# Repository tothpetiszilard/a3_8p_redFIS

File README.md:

# Audi A3 8P Red FIS Project
<b>This is a project about discovering (reverse-engineering) Audi A3 8P dashboard's Driver Information System and its protocol.</b>

For people who don't know what is DIS or FIS:
https://www.youtube.com/watch?v=bKFak5AGAGo

The goal is to implement a similiar but simpler open-source alternative to the "FIS-Control" or "Polar FIS".<br>
https://fis-control.de/index_en.html<br>
https://www.urotuning.com/products/polar-fis-advanced-multi-function-display-pf-04?variant=8384889323575

<b> Picture about the current status:</b><br>

## Connections description
https://github.com/tothpetiszilard/a3_8p_redFIS/blob/main/connection.md

## Compatibility:
Selectable in "menuconfig":
- You can use Alternative VWTP CANID if you have RNS-E (Audi navigation with color display) installed and your dashboards part number is "8P0 920 930". Don't select "FIS-Control" in your RNS-E custom firmware in this case. Enter/exit FIS scenarios are a bit buggy.

- You have to use Navigation VWTP CANID if you have dashboard with part number "8P0 920 931". Alternative CANID is not supported by the dash. 

You may select "FIS-Control" in your RNS-E custom firmware in this case, and RedFIS will do the routing of the display data from RNS-E to the Dash - if that last "page" is selected using the Up/Down stalk buttons. This feature can be enabled (or disabled) in the menuconfig.
Default state is enabled, since my car has a navigation with custom firmware and "FIS-Control" option enabled.

<i>Brave volunteers are warmly welcomed for testing... :)</i>

Used and helpful sources:<br>
https://docs.google.com/spreadsheets/d/1eirT8LbSRl4j06BpwgsiE4PM_2BGH9UStdWLXwKvHJw/edit#gid=10<br>
https://i-wiki.tech/?post=vw-transport-protocol-20-tp-20-for-can-bus<br>
http://www.orlaus.dk/mercantec/UdvidetHardwareSoftware/Can/OBD2/VW%20Transport%20Protocol%202.0%20(TP%202.0)%20for%20CAN%20bus%20_%20jazdw.pdf<br>
https://github.com/openvehicles/Open-Vehicle-Monitoring-System-3/blob/master/vehicle/OVMS.V3/components/vehicle/docs/VW-TP-2.0.txt<br>

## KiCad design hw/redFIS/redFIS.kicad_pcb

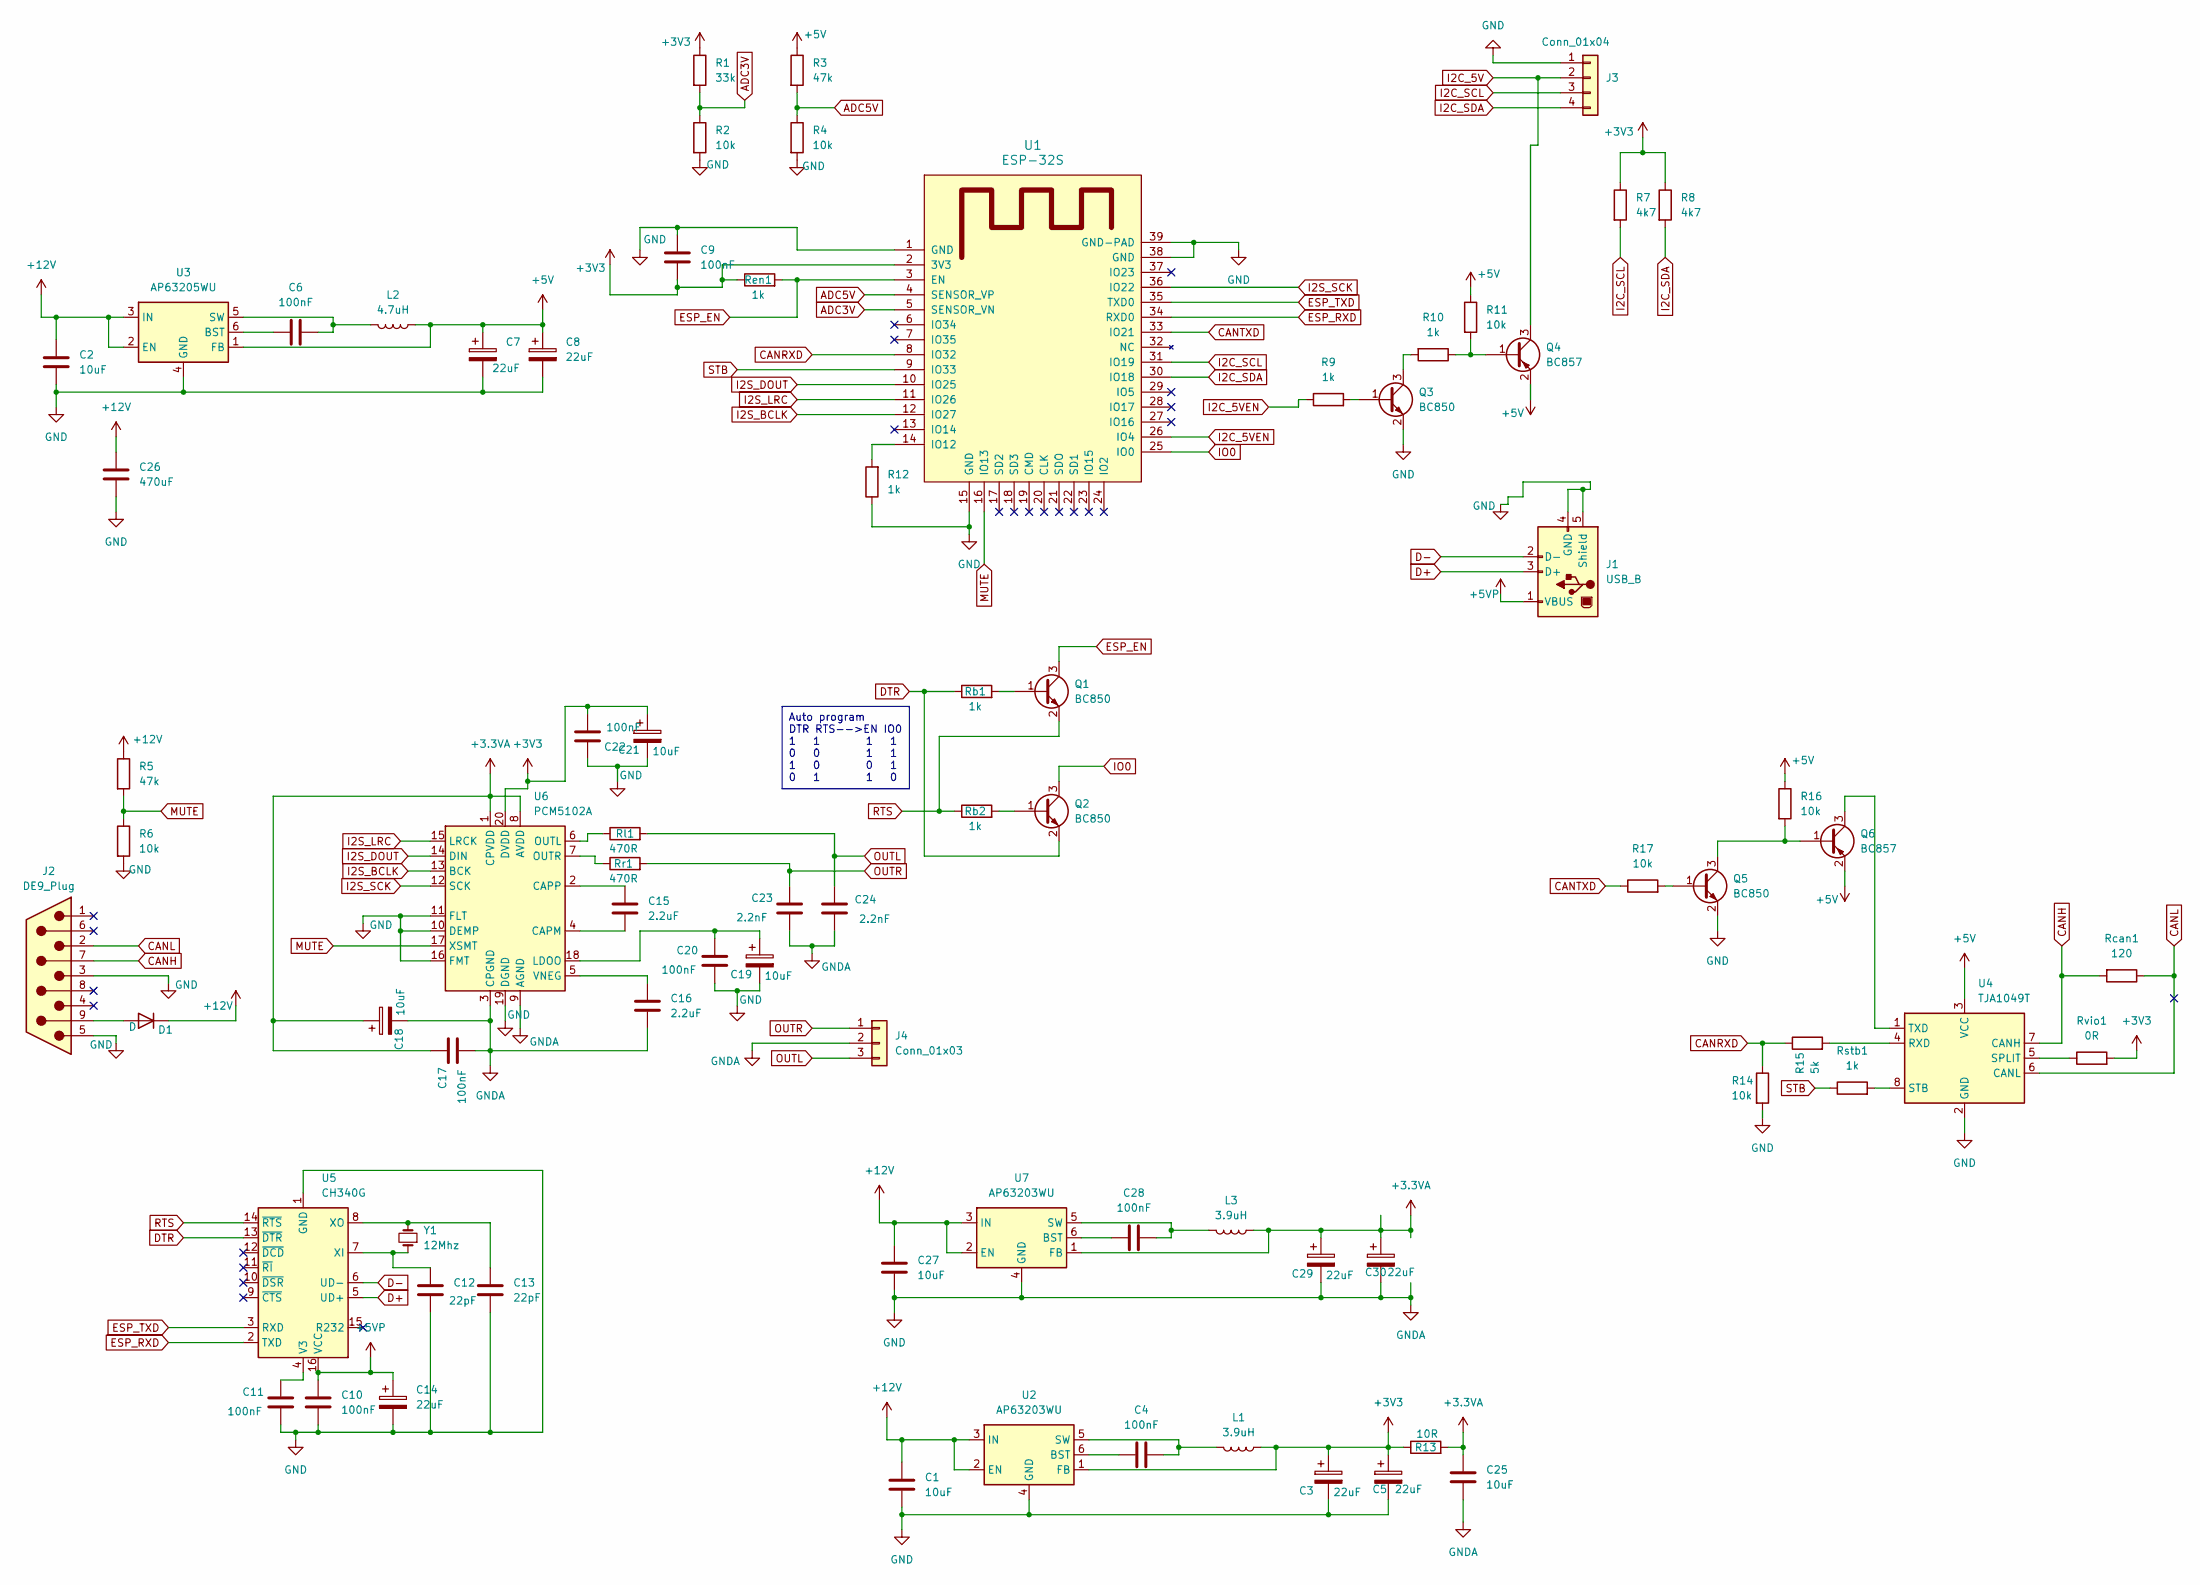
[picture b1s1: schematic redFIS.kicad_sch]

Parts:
C1, C2, C18, C19, C21, C25, C27: 10uF; C_0603_1608Metric_Pad1.08x0.95mm_HandSolder
C3, C5, C7, C8, C14, C29, C30: 22uF; C_1210_3225Metric_Pad1.33x2.70mm_HandSolder
C4, C6, C9, C10, C11, C17, C20, C22, C28: 100nF; C_0603_1608Metric_Pad1.08x0.95mm_HandSolder
C12, C13: 22pF; C_0603_1608Metric_Pad1.08x0.95mm_HandSolder
C15, C16: 2.2uF; C_0603_1608Metric_Pad1.08x0.95mm_HandSolder
C23, C24: 2.2nF; C_0603_1608Metric_Pad1.08x0.95mm_HandSolder
C26: 470uF; CP_Radial_D16.0mm_P7.50mm
D1: D; D_SMB_Handsoldering
J1: USB_B; USB_B_OST_USB-B1HSxx_Horizontal
J2: DE9_Plug; DSUB-9_Male_EdgeMount_P2.77mm
J3: Conn_01x04; PinHeader_1x04_P2.54mm_Vertical
J4: Conn_01x03; PinHeader_1x03_P2.54mm_Vertical
L1, L3: 3.9uH; L_TracoPower_TCK-047_5.2x5.8mm
L2: 4.7uH; L_TracoPower_TCK-047_5.2x5.8mm
Q1, Q2: BC850; SOT-23_Handsoldering
Q3, Q5: BC850; SOT-23
Q4, Q6: BC857; SOT-23
R1: 33k; R_0603_1608Metric_Pad0.98x0.95mm_HandSolder
R2, R4, R6, R11, R14, R16, R17: 10k; R_0603_1608Metric_Pad0.98x0.95mm_HandSolder
R3, R5: 47k; R_0603_1608Metric_Pad0.98x0.95mm_HandSolder
R7, R8: 4k7; R_0603_1608Metric_Pad0.98x0.95mm_HandSolder
R9, R10, R12: 1k; R_0603_1608Metric_Pad0.98x0.95mm_HandSolder
R13: 10R; R_1206_3216Metric_Pad1.30x1.75mm_HandSolder
R15: 5k; R_0603_1608Metric_Pad0.98x0.95mm_HandSolder
Rb1, Rb2: 1k; R_0603_1608Metric_Pad0.98x0.95mm_HandSolder
Rcan1: 120; R_0603_1608Metric_Pad0.98x0.95mm_HandSolder
Ren1: 1k; R_0603_1608Metric_Pad0.98x0.95mm_HandSolder
Rl1: 470R; R_0603_1608Metric_Pad0.98x0.95mm_HandSolder
Rr1: 470R; R_0603_1608Metric_Pad0.98x0.95mm_HandSolder
Rstb1: 1k; R_0603_1608Metric_Pad0.98x0.95mm_HandSolder
Rvio1: 0R; R_0603_1608Metric_Pad0.98x0.95mm_HandSolder
U1: ESP-32S
U2, U7: AP63203WU; TSOT-23-6
U3: AP63205WU; TSOT-23-6
U4: TJA1049T; SOIC-8_3.9x4.9mm_P1.27mm
U5: CH340G; SOIC-16_3.9x9.9mm_P1.27mm
U6: PCM5102A; TSSOP-20_4.4x6.5mm_P0.65mm
Y1: 12Mhz; Crystal_SMD_HC49-SD_HandSoldering

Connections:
+3.3VA: C17.2, C18.1, C25.1, C29.1, C30.1, L3.1, R13.2, U6.1 (CPVDD), U6.8 (AVDD), U7.1 (FB)
+3V3: C3.1, C5.1, C9.1, C21.1, C22.1, L1.1, R1.1, R7.1, R8.1, R13.1, Ren1.1, Rvio1.2, U1.2 (3V3), U2.1 (FB), U6.20 (DVDD)
+5V: C7.1, C8.1, L2.1, Q4.2 (E), Q6.2 (E), R3.1, R11.1, R16.1, U3.1 (FB), U4.3 (VCC)
+5VP: C10.2, C14.1, J1.1 (VBUS), U5.16 (VCC)
+12V: C1.1, C2.1, C26.1, C27.1, D1.1 (K), R5.1, U2.2 (EN), U2.3 (IN), U3.2 (EN), U3.3 (IN), U7.2 (EN), U7.3 (IN)
ADC3V: R1.2, R2.1, U1.5 (SENSOR_VN)
ADC5V: R3.2, R4.1, U1.4 (SENSOR_VP)
CANH: J2.7, Rcan1.2, U4.7 (CANH)
CANL: J2.2, Rcan1.1, U4.6 (CANL)
CANRXD: R14.1, R15.1, U1.8 (IO32)
CANTXD: R17.1, U1.33 (IO21)
D+: J1.3 (D+), U5.5 (UD+)
D-: J1.2 (D-), U5.6 (UD-)
DTR: Q2.2 (E), Rb1.1, U5.13 (~DTR)
ESP_EN: Q1.3 (C), Ren1.2, U1.3 (EN)
ESP_RXD: U1.34 (RXD0), U5.2 (TXD)
ESP_TXD: U1.35 (TXD0), U5.3 (RXD)
GND: C1.2, C2.2, C3.2, C5.2, C7.2, C8.2, C9.2, C10.1, C11.1, C12.1, C13.1, C14.2, C16.2, C17.1, C18.2, C19.2, C20.1, C21.2, C22.2, C23.1, C24.1, C25.2, C26.2, C27.2, C29.2, C30.2, J1.4 (GND), J1.5 (Shield), J2.3, J2.5, J3.1, J4.2, Q3.2 (E), Q5.2 (E), R2.2, R4.2, R6.2, R12.1, R14.2, U1.1 (GND), U1.15 (GND), U1.38 (GND), U1.39 (GND-PAD), U2.4 (GND), U3.4 (GND), U4.2 (GND), U5.1 (GND), U6.3 (CPGND), U6.9 (AGND), U6.10 (DEMP), U6.11 (FLT), U6.16 (FMT), U6.19 (DGND), U7.4 (GND)
I2C_5V: J3.2, Q4.3 (C)
I2C_5VEN: R9.1, U1.26 (IO4)
I2C_SCL: J3.3, R7.2, U1.31 (IO19)
I2C_SDA: J3.4, R8.2, U1.30 (IO18)
I2S_BCLK: U1.12 (IO27), U6.13 (BCK)
I2S_DOUT: U1.10 (IO25), U6.14 (DIN)
I2S_LRC: U1.11 (IO26), U6.15 (LRCK)
I2S_SCK: U1.36 (IO22), U6.12 (SCK)
IO0: Q2.3 (C), U1.25 (IO0)
MUTE: R5.2, R6.1, U1.16 (IO13), U6.17 (XSMT)
unnamed: D1.2 (A), J2.9
unnamed: Q1.1 (B), Rb1.2
unnamed: Q2.1 (B), Rb2.2
unnamed: Q3.1 (B), R9.2
unnamed: Q3.3 (C), R10.2
unnamed: Q4.1 (B), R10.1, R11.2
unnamed: Q5.1 (B), R17.2
unnamed: Q5.3 (C), Q6.1 (B), R16.2
unnamed: Q6.3 (C), U4.1 (TXD)
unnamed: R12.2, U1.14 (IO12)
unnamed: C4.1, U2.6 (BST)
unnamed: C4.2, L1.2, U2.5 (SW)
unnamed: C6.1, U3.6 (BST)
unnamed: C6.2, L2.2, U3.5 (SW)
unnamed: R15.2, U4.4 (RXD)
unnamed: Rvio1.1, U4.5 (SPLIT)
unnamed: Rstb1.2, U4.8 (STB)
unnamed: C11.2, U5.4 (V3)
unnamed: C12.2, U5.7 (XI), Y1.1
unnamed: C13.2, U5.8 (XO), Y1.2
unnamed: C15.2, U6.4 (CAPM)
unnamed: C15.1, U6.2 (CAPP)
unnamed: C19.1, C20.2, U6.18 (LDOO)
unnamed: Rl1.1, U6.6 (OUTL)
unnamed: Rr1.1, U6.7 (OUTR)
unnamed: C16.1, U6.5 (VNEG)
unnamed: C28.1, U7.6 (BST)
unnamed: C28.2, L3.2, U7.5 (SW)
OUTL: C24.2, J4.3, Rl1.2
OUTR: C23.2, J4.1, Rr1.2
RTS: Q1.2 (E), Rb2.1, U5.14 (~RTS)
STB: Rstb1.1, U1.9 (IO33)

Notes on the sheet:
Auto program DTR RTS-->EN IO0 1 1 1 1 0 0 1 1 1 0 0 1 0 1 1 0

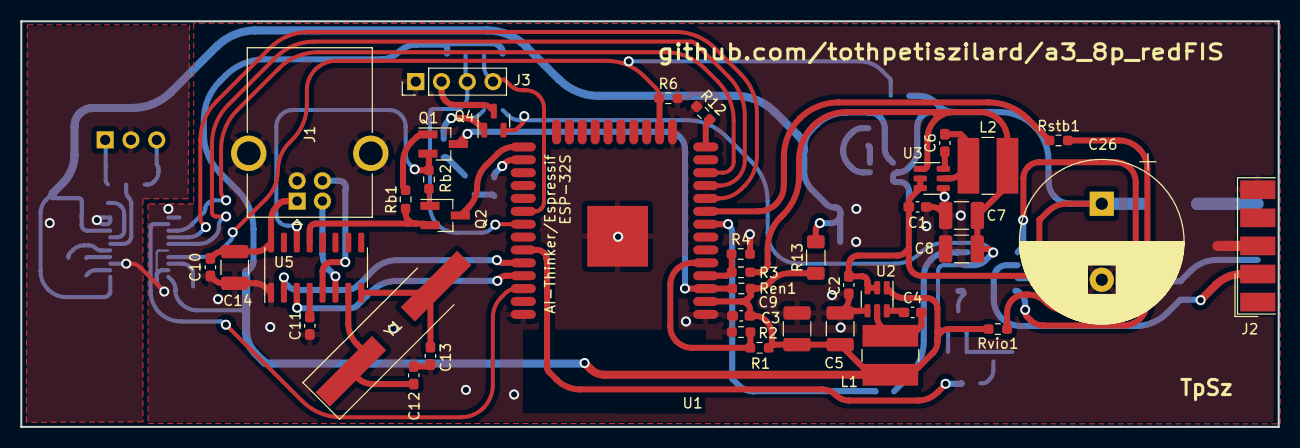
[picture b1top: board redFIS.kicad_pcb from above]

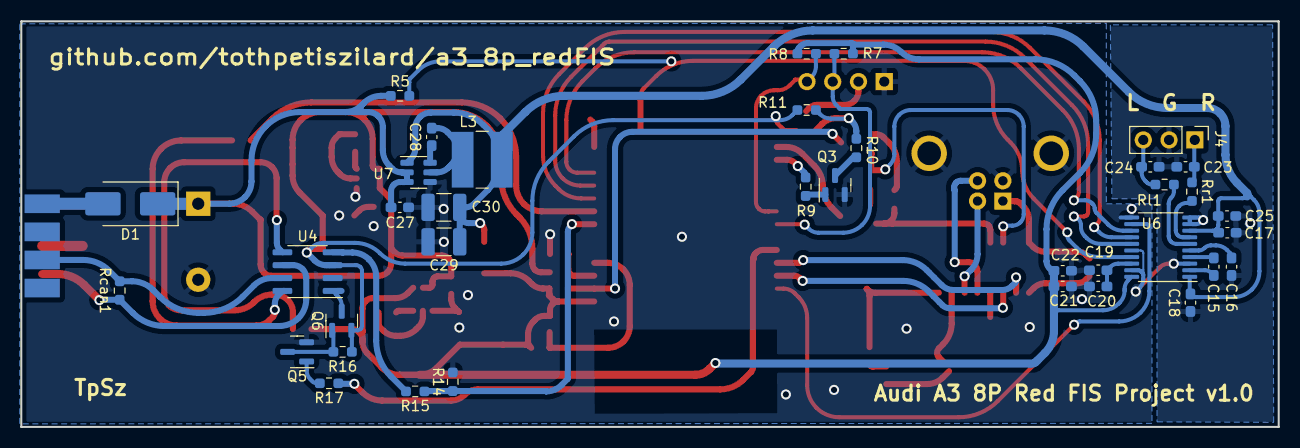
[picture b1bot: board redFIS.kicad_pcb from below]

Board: 2 copper layers, 124.0 x 40.0 mm, 77 parts (37 on the bottom side), 60 nets.

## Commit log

2022-11-19 Update README.md
    Update project description
2022-11-19 Added some collected information as text documents
2022-11-19 No duplicates
2022-11-23 Started coding: VwTP + CAN wrapper added -> test results: TP channel can be opened
2022-11-24 First running 'demo' version on ESP32 hw, no real functionality yet, just a feasibility study
2022-11-24 Added evidence on that it works
2022-11-24 Added picture
2022-11-24 Bugfixes: VWTP: Resend + wait for ack; DashApp: switched to small font as the comment says
2022-11-24 Configured CAN acceptance filter
2022-11-24 Added support for stalk buttons
2022-11-24 Started implementation of kwp2000 diagnostics support
2022-11-25 VWTP improvements and bugfix for diagnostics
2022-11-28 Feature update for DashApp, improved robustness for the project
2022-11-28 VWTP feature upgrade
2022-11-28 Bugfixes + ASCII fix added
2022-12-05 Not the cleanest code ever, but does something
2022-12-05 Replaced image in description
2022-12-08 Improved stability, removed debug code
2022-12-09 Little bugfixes and VWTP upgrade
2022-12-09 VWTP improvements
2022-12-09 KWP2000: Handling timeouts, try reconnect if needed, handling corrupt TP packets
2022-12-14 Single-thread version of the software for testing purposes
2022-12-22 Bugfix: KWP2000 timeout handling was incorrect
2022-12-22 Increased CAN RX buffer size
2022-12-22 Fixed a bug in Kwp2000 timeout handling
2022-12-22 Bad bugfix..
2022-12-23 Update canWrapper.c
    Fixing a huge but well hidden bug. CAN of course shall resend the frame if it lost the arbitration ...
2022-12-23 Fixed a well hidden bug in CAN config
2022-12-24 Added page switching to DIS
2022-12-24 Fix build
2022-12-24 Update DIS
2022-12-24 Remove debug code, slight improvements
2023-03-22 Added ignition detection to DashApp and KWP, adapted can filter, did some changes on DIS
2023-03-23 Primitive ignition handling and sleep mode with wakeup on CAN msg
2023-03-24 Added new menuconfig, now navigation or auto transmission channel can be selected. Adapted code accordingly. Added enter/exit feature (necessary while using auto trans ch)
2023-03-25 Fixed namings - wrong assumption
2023-03-25 Updated README for version 0.2
2023-03-25 Cosmetics in README
2023-03-25 Excluding KL_S from ignition status
2023-03-26 Cosmetics - Added comments
2023-03-26 Redesigned diagnostics - added dashboard diag module
2023-03-26 Updated KWP2000 module
2023-03-26 Added 'Bench test mode'
2023-12-21 Started unit-tests for VWTP component
2023-12-21 Undate code to v0_2, unstable version
2023-12-21 VWTP fixes and more unit-tests
2023-12-21 Add more test-cases for VWTP
2023-12-21 Added unit-test for stalk_buttons
2023-12-22 Added unit-test for DashApp
2023-12-22 Improved bench test mode in DIS
2023-12-25 Small fixes in the 'old' code
2023-12-25 Up and Down stalkbuttons were mixed up
2023-12-25 Beta version of VWTP routing between Nav and Dash
2024-06-23 New routing concept - NOT TESTED YET
2024-07-04 New routing concept - Bugfix
2024-07-04 Bugfix for switching between diag and nav routing screens
2024-07-07 Nav to dash gateway/routing concept redesigned because of failures
2024-07-07 Bugfixes for DIS event handling (still have room for improvement) and implemented a missing VWTP function for routing
2024-07-07 Improved menuconfig, updated README, ready for pull-request :)
2024-12-15 Started HW design in KiCAD
2024-12-15 Changes in schematic
2024-12-17 Worked on HW design - layout
2024-12-18 Corrected bench test mode ignition message incorrect value - bugfix
2024-12-19 Finished first version of PCB
2024-12-20 HW design bugfix
2024-12-20 Finished bugfixing of HW design v1
2024-12-20 PCB update - Almost forget to round the tracks...
2024-12-20 PCB - Label movement on silkscreen
2025-12-21 Some modifications to be able to play with the 8P cluster bootloaders
2025-12-21 Added connection description
2025-12-21 Update documentation
    Update README.md
    Update connection.md
    Update connection.md
2025-12-21 Adaptations for development on a Mac
2025-12-21 Migration to the new esp-idf twai driver
